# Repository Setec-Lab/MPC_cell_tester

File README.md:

# MPC_cell_tester
Desarrollo de un sistema embebido para el control y regulación del proceso dinámico de carga y descarga de celdas electroquímicas y su posterior validación para satélites CubeSat de 1U.

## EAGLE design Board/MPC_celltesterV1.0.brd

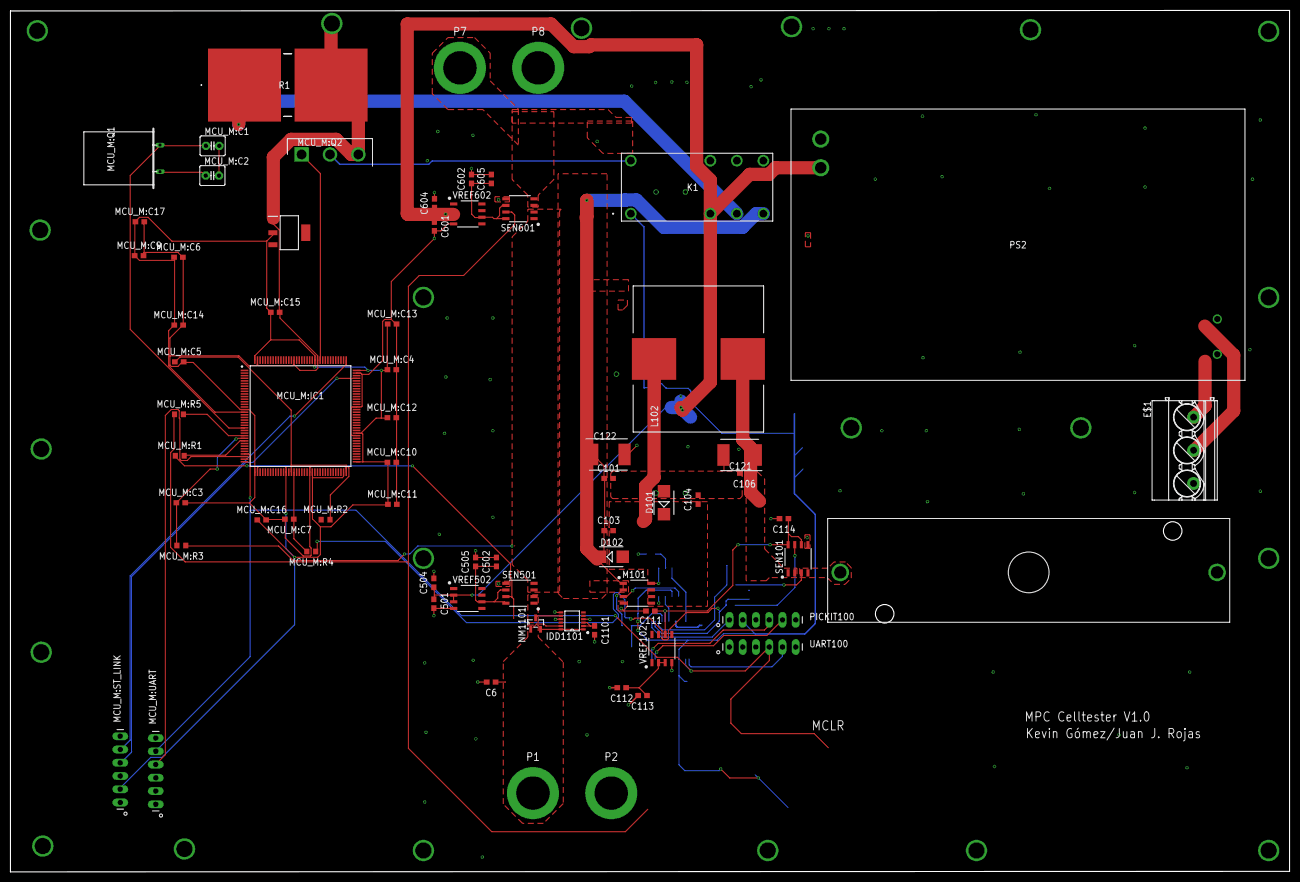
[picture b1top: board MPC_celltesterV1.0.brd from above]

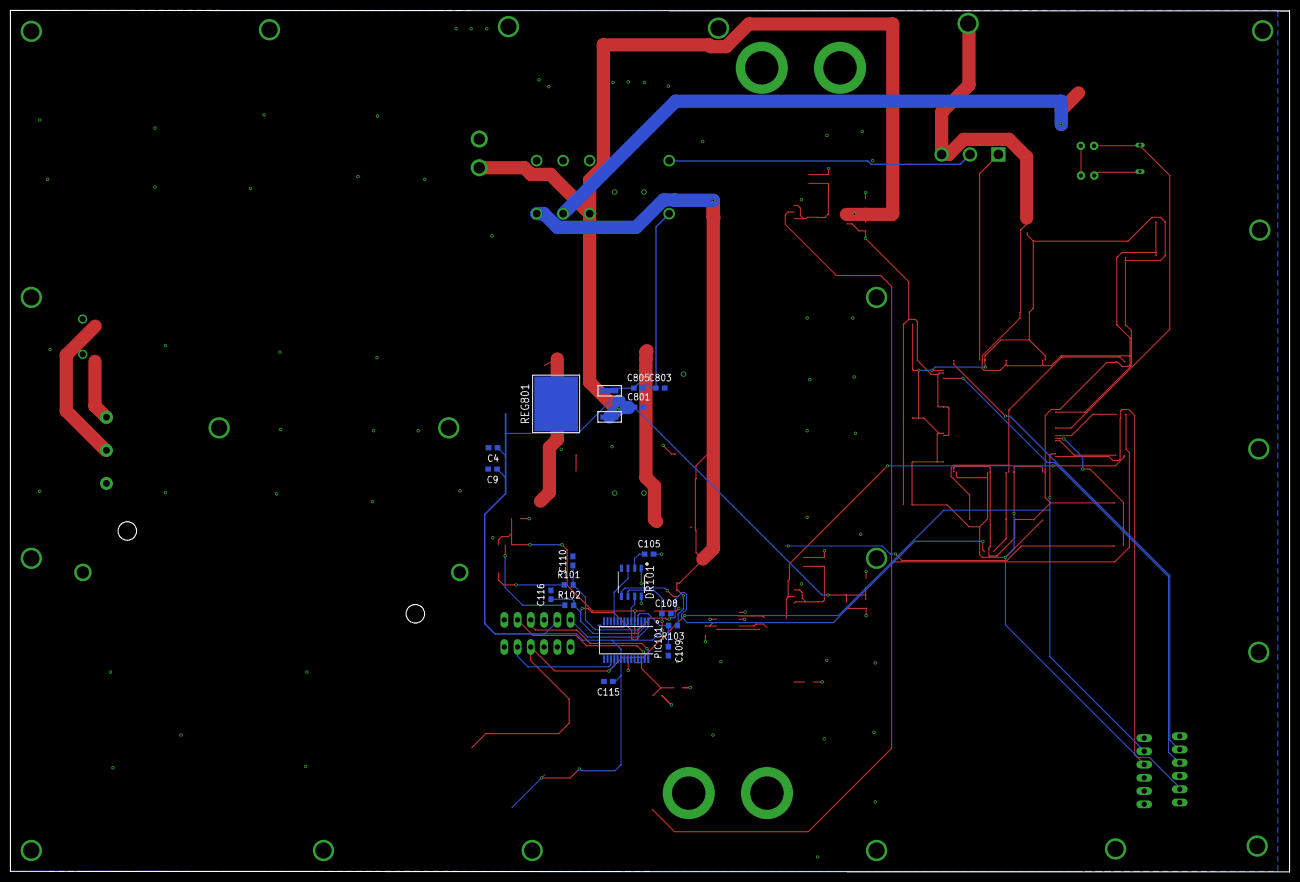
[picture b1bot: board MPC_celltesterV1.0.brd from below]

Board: 2 copper layers, 245.2 x 165.1 mm, 87 parts (17 on the bottom side), 46 nets.

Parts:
C4, C109, C110, C114, C115, C505, C605, C1101: 0.1u; C0603
C6, C101, C105, C106, C111, C113, C502, C504, C602, C604, C803: 1u; C0603
C9, C112, C501, C601, C805: 10u; C0603
C103, C104, C116: 1n; C0603
C108: 2.2u; C0603
C121, C122: T543O477M016AHE020; CAPPM7360X430N
C801: 0.33u; C0603
CELL1: CELL18650_HOLDER; 18650_HOLDER
D101, D102: SMB
DR101: TPS28225D; SOIC-8
E$1: MKDS_5/3-635
IDD1101: LTC4352CMS; MSOP12
K1: ADJ56005
L102: 74437529203471; 74437529203221
M101: SI4914BDY; SOIC-8
MCU_M:C1, MCU_M:C2: 22pF; C2.5-4
MCU_M:C3, MCU_M:C5: 0.1u; C0603
MCU_M:C4, MCU_M:C6, MCU_M:C9, MCU_M:C10, MCU_M:C11, MCU_M:C12, MCU_M:C13, MCU_M:C14, MCU_M:C15, MCU_M:C16, MCU_M:C17: 1u; C0603
MCU_M:C7: 1n; C0603
MCU_M:IC1: STM32U575ZIT6Q; QFP50P2200X2200X160-144N
MCU_M:IC2: REG1117-3.3; SOT230P700X180-4N
MCU_M:Q1: Q
MCU_M:Q2: IMW65R083M1HXKSA1; TO544P530X1590X2600-3P
MCU_M:R1, MCU_M:R4, MCU_M:R5: 0; R0603
MCU_M:R2, MCU_M:R3: 200; R0603
MCU_M:ST_LINK: MA06-1
MCU_M:UART: MA06-1
NM1101: IRLML6244TRPBF; SOT-23
P1, P2, P7, P8: TJ-563
PIC101: PIC16F1786-I/SS; SSOP28
PICKIT100: MA06-1
PS2: MPM-90-12; MPM9012
R1: RWS10_8K2_J_T_R; RWS108K2JTR
R101, R103: 200; R0603
R102: 0; R0603
REG801: NCV7805BD2TG; D2PAK-3
SEN101, SEN501, SEN601: ACS723-05AB-T; SOIC-8
UART100: MA06-1
VREF102, VREF502, VREF602: REF195GSZ; SOIC-8

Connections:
+5V: C4.1, C9.1, C108.1, C115.1, C803.1, C805.1, DR101.6, K1.1, PIC101.20, PICKIT100.2, REG801.3
+12V: C112.1, C113.1, C501.1, C504.1, C601.1, C604.1, C801.1, K1.2, PS2.4, REG801.1, VREF102.2, VREF102.3, VREF502.2, VREF502.3, VREF602.2, VREF602.3
COM_RX: MCU_M:IC1.33, MCU_M:UART.5, PIC101.18, UART100.4
GND: C4.2, C6.2, C9.2, C101.2, C104.2, C106.2, C108.2, C109.2, C110.2, C111.2, C112.2, C113.2, C114.2, C115.2, C116.2, C121.2, C122.2, C501.2, C502.2, C504.2, C505.2, C601.2, C602.2, C604.2, C605.2, C801.2, C803.2, C805.2, C1101.2, CELL1.BB1.N, D101.A, DR101.4, IDD1101.4, IDD1101.7, IDD1101.9, M101.4, MCU_M:C3.2, MCU_M:C4.2, MCU_M:C5.2, MCU_M:C6.2, MCU_M:C7.2, MCU_M:C9.2, MCU_M:C10.2, MCU_M:C11.2, MCU_M:C12.2, MCU_M:C13.2, MCU_M:C14.2, MCU_M:C15.2, MCU_M:C16.2, MCU_M:C17.2, MCU_M:IC1.16, MCU_M:IC1.37, MCU_M:IC1.48, MCU_M:IC1.58, MCU_M:IC1.72, MCU_M:IC1.83, MCU_M:IC1.94, MCU_M:IC1.107, MCU_M:IC1.120, MCU_M:IC1.129, MCU_M:IC1.143, MCU_M:IC2.1, MCU_M:Q2.3, MCU_M:ST_LINK.3, MCU_M:UART.1, P2.P, P8.P, PIC101.8, PIC101.19, PICKIT100.3, PS2.3, R1.2, REG801.4, SEN101.5, SEN501.5, SEN601.5, UART100.1, VREF102.4, VREF502.4, VREF602.4
IDEAL_D1:N$1: IDD1101.1, IDD1101.12, NM1101.2
IDEAL_D1:N$4: C1101.1, IDD1101.2, IDD1101.3
IS_LOAD: MCU_M:R5.1, SEN601.7
IS_PV: MCU_M:R1.1, SEN501.7
I_BAT: R102.1, SEN101.7
LOAD_BUS: P7.P, SEN601.3, SEN601.4
MCU_M:3.3V_IN: MCU_M:C4.1, MCU_M:C6.1, MCU_M:C9.1, MCU_M:C10.1, MCU_M:C11.1, MCU_M:C12.1, MCU_M:C13.1, MCU_M:C14.1, MCU_M:C15.1, MCU_M:C16.1, MCU_M:C17.1, MCU_M:IC1.17, MCU_M:IC1.38, MCU_M:IC1.49, MCU_M:IC1.59, MCU_M:IC1.71, MCU_M:IC1.73, MCU_M:IC1.84, MCU_M:IC1.108, MCU_M:IC1.121, MCU_M:IC1.144, MCU_M:IC2.2, MCU_M:ST_LINK.2
MCU_M:IS_BATC: MCU_M:C7.1, MCU_M:IC1.52, MCU_M:R4.2
MCU_M:I_LOAD: MCU_M:IC1.26, MCU_M:R5.2
MCU_M:I_PV: MCU_M:IC1.28, MCU_M:R1.2
MCU_M:N$20: MCU_M:C1.1, MCU_M:IC1.23, MCU_M:Q1.2
MCU_M:N$21: MCU_M:C2.1, MCU_M:Q1.1
MCU_M:N$22: MCU_M:C1.2, MCU_M:C2.2
MCU_M:N$27: MCU_M:IC1.119, MCU_M:Q2.1
MCU_M:RX: MCU_M:IC1.34, MCU_M:UART.4
MCU_M:SW_CLK: MCU_M:IC1.109, MCU_M:ST_LINK.5
MCU_M:SW_DIO: MCU_M:IC1.105, MCU_M:ST_LINK.4
MCU_M:VS_BATC: MCU_M:C5.1, MCU_M:IC1.51, MCU_M:R2.2
MCU_M:V_BUS: MCU_M:C3.1, MCU_M:IC1.27, MCU_M:R3.2
MCU_S1:5V_REF: C111.1, C114.1, PIC101.5, SEN101.6, SEN101.8, VREF102.6
MCU_S1:DR_EN: DR101.7, PIC101.6
MCU_S1:G1: DR101.1, M101.8
MCU_S1:G2: DR101.5, M101.3
MCU_S1:ICSPCLK: PIC101.27, PICKIT100.5
MCU_S1:ICSPDAT: PIC101.28, PICKIT100.4
MCU_S1:IS_BAT: C116.1, PIC101.2, R102.2
MCU_S1:LO: C106.1, C121.1, L102.2, SEN101.1, SEN101.2
MCU_S1:MCLR: PIC101.1, PICKIT100.1
MCU_S1:N$2: C105.1, DR101.2
MCU_S1:PWM: DR101.3, PIC101.11
MCU_S1:SW: C103.2, C104.1, C105.2, D101.C, D102.A, DR101.8, L102.1, M101.5, M101.6, M101.7
MCU_S1:TX: PIC101.17, UART100.5
MCU_S1:VS_BAT: C110.1, PIC101.3, R101.2
MCU_S1:VS_BUS: C109.1, PIC101.4, R103.2
unnamed: CELL1.BB1.P, R101.1, SEN101.3, SEN101.4
unnamed: K1.3, R1.1
unnamed: IDD1101.8, NM1101.3, SEN501.1, SEN501.2
PV: C6.1, IDD1101.11, NM1101.1, P1.P
PV_BUS: C101.1, C103.1, C122.1, D102.C, K1.4, M101.1, M101.2, MCU_M:R3.1, R103.1, SEN501.3, SEN501.4, SEN601.1, SEN601.2
SENS_LOAD:5V_REF: C602.1, C605.1, SEN601.6, SEN601.8, VREF602.6
SENS_PV:5V_REF: C502.1, C505.1, SEN501.6, SEN501.8, VREF502.6
TX_RELAY: K1.8, MCU_M:Q2.2

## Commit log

2022-05-16 Digital controller design
2022-05-16 Código funcional del Bidirectional Buck converter
2022-05-23 Configuración de tiempos con nuevo diseño de control
2022-05-31 digital_controller funcional para el voltaje
2022-08-10 errors fixed
2022-09-30 voltage controller done in the correct way
2022-10-24 PID & PI constants enhaced
2022-11-06 Optimized code
2022-11-06 Board & renders implementation
2023-03-10 Librerías de Eagle actualizadas
